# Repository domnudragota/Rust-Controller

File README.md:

# Project Name
GamePad/Controller
## Description

Simple GamePad built on a breadboard to test in games. Is built on Windows XInput API, so it will detect it as an XBOX Controller. The purpose of this project is (besides building a controller) to test input latency in different games and on different systems, computers and monitors in order to see the difference in input latency. Will also compare with an actual Xbox Series controller.

## Hardware

<!-- Fill out this table with all the hardware components that you mght need.

The format is 
```
| [Device](link://to/device) | This is used ... | [price](link://to/store) |

```

-->

| Device | Usage | Price |
|--------|--------|-------|
| [Rapspberry Pi Pico W](https://www.raspberrypi.com/documentation/microcontrollers/raspberry-pi-pico.html) | The microcontroller | [35 RON](https://www.optimusdigital.ro/en/raspberry-pi-boards/12394-raspberry-pi-pico-w.html) |
| BreadBoard | Build the circuit | [10 RON] https://www.optimusdigital.ro/ro/prototipare-breadboard-uri/8-breadboard-830-points.html |
| Buttons ( 12-15 ) | Input for controller | [5 RON] https://www.optimusdigital.ro/ro/butoane-i-comutatoare/1119-buton-6x6x6.html?search_query=buton&results=222 |
| Resistances | To not fry the circuit | [5 RON] https://www.optimusdigital.ro/ro/componente-electronice-rezistoare/858-rezistor-025w-18k.html?search_query=rezistor&results=120 |
| 2x JoySticks | Move and aim with the controller | [10 RON] https://www.optimusdigital.ro/ro/senzori-senzori-de-atingere/742-modul-joystick-ps2-biaxial-negru-cu-5-pini.html?search_query=joystick&results=42 |

## Links

<!-- Add a few links that got you the idea and that you think you will use for your project -->

1. [link](https://learn.microsoft.com/en-us/windows/win32/xinput/getting-started-with-xinput)
2. [link](https://www.howtogeek.com/792984/directinput-vs.-xinput-for-game-controllers-whats-the-difference/)
...

# Software and Code

### Rust Code for Raspberry Pi Pico W
The Rust code deployed on the Raspberry Pi Pico W reads button presses and joystick movements, packaging them into a structured format to be sent over UDP.

## Run the code
* Open the lab-main-Copy-Copy file in which IDE you desire (I used RustRover for this project)
* The code is located in /lab08/lab08_ex3_4/src/main.rs

⚠️ **Warning:** Ensure change the IP adresses and the path target to the cyw43-firmware in the code before you build it. Also the ID and the password of the network. Make sure the band of the network is 2.4GHZ!

```rust
let fw = include_bytes!("C:/Users/Andrei/Desktop/lab-main/cyw43-firmware/43439A0.bin");
let clm = include_bytes!("C:/Users/Andrei/Desktop/lab-main/cyw43-firmware/43439A0_clm.bin");

```

```rust
//change the ip adress as well

match socket
            .send_to(
                &packet,
                //here
                IpEndpoint::new(IpAddress::v4(192, 555, 553, 555), 1234), 
            )
            .await
        {
            Ok(()) => {
                info!("sent")
            }
            Err(e) => {
                warn!("send error: {:?}", e);
            }
        }
        info!("Sending packet to UDP server...");

        //match for joystick
        match socket.send_to(&packet, IpEndpoint::new
        //and here
        (IpAddress::v4(192, 555, 555, 555), 1234)).await {
            Ok(()) => info!("Joystick data sent"),
            Err(e) => warn!("send error: {:?}", e),
         }

    }
```
```rust
//change the network

const WIFI_NETWORK: &str = "da";
const WIFI_PASSWORD: &str = "da";
```

## Building the code
* Open a terminal and make sure you are in the correct directory 

⚠️ **Warning:** Please double check if the terminal correctly detects the directory (including the -Copy - Copy sufixes of the name), otherwise it won't build correctly

* To make sure you are in the correct file, use these commands

```
cd '.\lab-main - Copy - Copy\lab08\lab08_ex3_4\
```
* To build the project, simply type in the terminal
```
cargo build --release --target=thumbv6m-none-eabi  
```
* When it compiles, we need to open an UDP server so that we can send the data.
* Open the _udpserver_ file as a **separate** project/tab.
* Run the server with _cargo run_
* Once the server is fully loaded, go back to the 1st project and type in the terminal in order to flash it on the Pico

```
elf2uf2-rs -d -s ..\..\target\thumbv6m-none-eabi\release\lab08_ex3_4

```
* When the Pico connects to the UDP server, it will constantly send packets to the server
* Now we need a "translator" to decode the packets

# Detecting the Controller on Windows

## Prerequisites

Before you begin setting up the project, ensure you have the following prerequisites installed on your system:

## System Requirements
- **Operating System**: Windows 10 or newer is recommended for full compatibility.

## Software Requirements
- **.NET Framework**: .NET 5.0 or later. Make sure to download and install it from [Microsoft's official site](https://dotnet.microsoft.com/download).
- **Visual Studio** or **Visual Studio Code**: For code editing and debugging. Visual Studio can be downloaded from [here](https://visualstudio.microsoft.com/downloads/).

## Driver Installation
- **ViGEmBus Driver**: This driver is required to create a virtual Xbox controller that the system recognizes.
  - Download the latest version of the ViGEmBus driver from the [ViGEmBus GitHub releases page](https://github.com/ViGEm/ViGEmBus/releases).
  - Follow the installation instructions provided there to install the driver on your system.

## Additional Libraries
- **Nefarius.ViGEm.Client**: This is a .NET library used to interact with the ViGEmBus driver programmatically.
  - Ensure your project references this library. It can be added via NuGet in Visual Studio or by running the following command in your project directory:
    ```bash
    dotnet add package Nefarius.ViGEm.Client
    ```

## Hardware Requirements
- If testing the project physically, ensure you have a compatible hardware setup, including a game controller or custom hardware interfacing with your PC.

Make sure all prerequisites are properly installed and configured before proceeding with the project setup.

# Opening the Project and Adding NuGet Packages

## Opening the C# Project in Visual Studio

To start working on the project, you need to open it in an Integrated Development Environment (IDE). Visual Studio is recommended for C# projects. Follow these steps to open the project:

1. **Launch Visual Studio**:
   - Open Visual Studio. If you haven't installed it yet, download it from [Visual Studio Downloads](https://visualstudio.microsoft.com/downloads/).

2. **Open Project or Solution**:
- Name of the C# code is _ConsoleApp1_
   - On the initial launch screen, click **Open a project or solution**.
   - Navigate to the folder where you have cloned or downloaded the project.
   - Select the `.sln` or `.csproj` file and click **Open** to load the project into Visual Studio.

## Adding a NuGet Package

NuGet is a package manager for .NET that enables developers to share and consume useful code. Adding a NuGet package to your project can extend its functionality easily. Here's how to add a NuGet package:

1. **Open NuGet Package Manager**:
   - Right-click on the project in the **Solution Explorer** in Visual Studio.
   - Click **Manage NuGet Packages**.

2. **Browse for Packages**:
   - Go to the **Browse** tab in the NuGet Package Manager.
   - Type the package name you want to install in the search box (e.g., `Nefarius.ViGEm.Client`).

3. **Install the Package**:
   - Select the package from the list of search results.
   - Click on the **Install** button next to the package details.
   - Review any license agreements, if prompted, and accept them to proceed with the installation.

4. **Verify Package Installation**:
   - After installation, the package will appear under the **Dependencies** > **NuGet** node in your project structure.
   - You can now use the functionalities provided by the NuGet package in your project code.

## Verifying the Setup

After opening the project and adding the necessary NuGet packages, build the project to verify that everything is set up correctly:

- Click on **Build** > **Build Solution** in the menu bar.
- Ensure that the build completes without errors.

Before running the code, make sure to clode **ONLY** the UDP server in Rust, as C# will throw an exception.

# Mapping the buttons
* Run the C# code and it will display all the "translated" packages that the PICO is sending. 
## Step 1: Connect Your USB Controller

First, you need to physically connect your USB controller to your Windows machine.

- **Plug the USB connector** of your controller into a free USB port on your computer.
- Wait for Windows to recognize the device and install any necessary drivers. This process is typically automatic.

## Step 2: Check Device Recognition

After connecting your controller, verify that Windows has recognized it.

- Open **Control Panel** by typing `Control Panel` in the Start menu and pressing Enter.
- Navigate to **Hardware and Sound** > **Devices and Printers**.
- Under **Devices**, look for your USB controller. It should be listed under "Devices" if Windows recognizes it properly.
- If Device Manager can't find it, search in the Start menu for "Set Up USB Controllers".

## Step 3: Calibrate Your Controller

To ensure optimal performance, you might need to calibrate your controller. Here’s how to do it:

- Right-click on your controller icon in **Devices and Printers** and select **Game controller settings**.
- In the Game Controllers window, select your controller and click **Properties**.
- In the Properties window, go to the **Settings** tab and click on **Calibrate**.
- Follow the on-screen instructions to complete the calibration process.

## Step 4: Test Your Controller

After calibration, it’s a good idea to test the controller to make sure all buttons and joysticks are working as expected.

- In the Properties window of your controller, switch to the **Test** tab.
- Test each button and joystick on your controller. As you press buttons and move joysticks, corresponding buttons should light up in the test screen, confirming their functionality.

That's pretty much it. Let me know if there are questions regarding the compilation process.

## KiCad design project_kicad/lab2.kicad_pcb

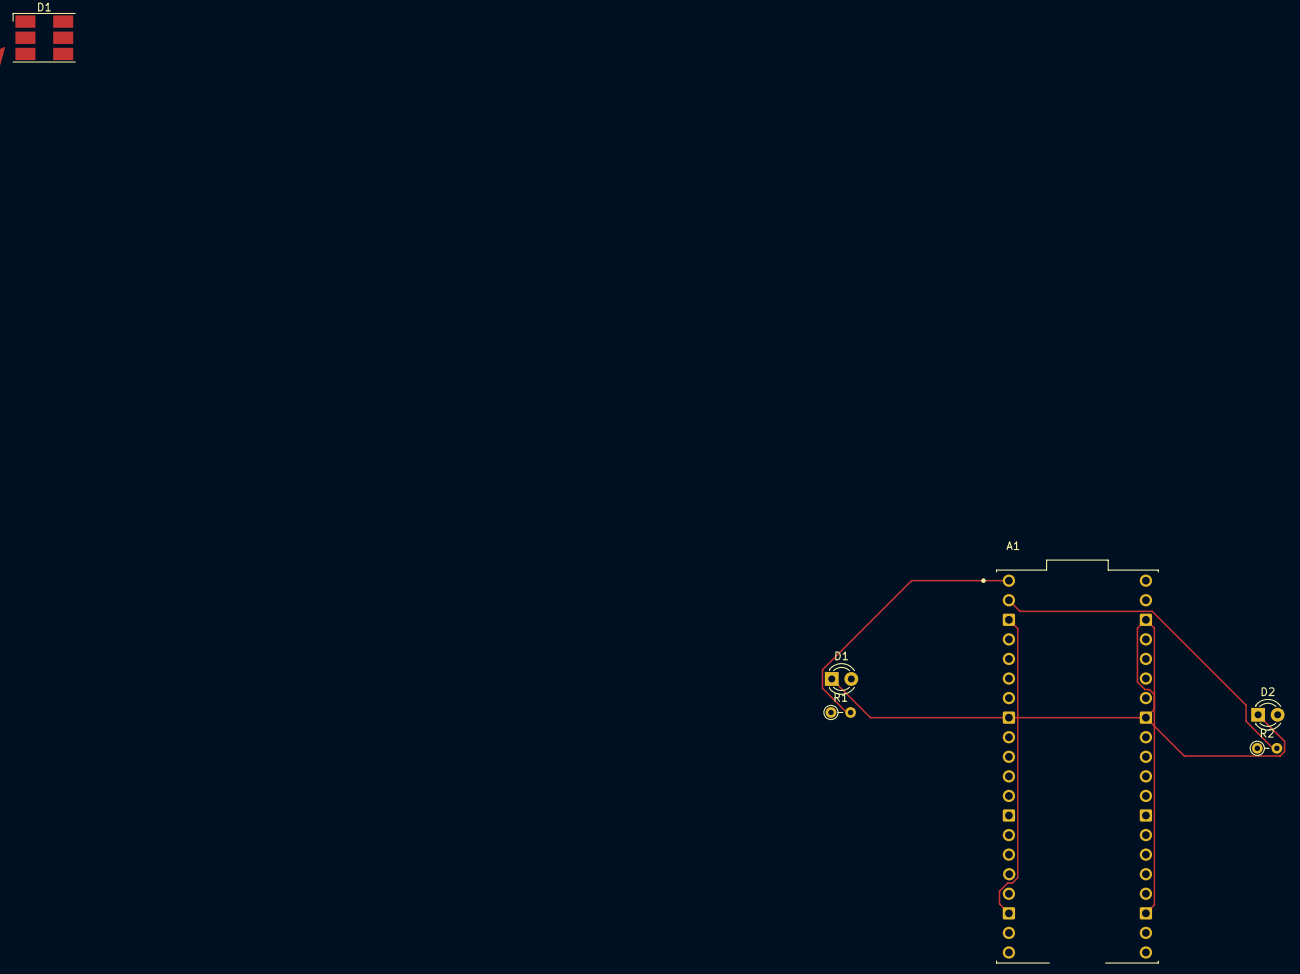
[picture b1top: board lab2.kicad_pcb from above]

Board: 2 copper layers, 7 parts (0 on the bottom side), 5 nets.

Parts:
A1: SC0918; MODULE_SC0918
D1, D2: LED; LED_D3.0mm
D1#2: LED_ARGB; LED_RGB_Cree-PLCC-6_6x5mm_P2.1mm
R1, R2: R; R_Axial_DIN0204_L3.6mm_D1.6mm_P2.54mm_Vertical
RN1: VoltageDivider; Symbol_HighVoltage_NoTriangle_6x15mm_Copper

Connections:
GND: A1.3 (GND), A1.8 (GND), A1.13 (GND), A1.18 (GND), A1.23 (GND), A1.28 (GND), A1.33 (AGND), A1.38 (GND), D1.1 (K), D2.1 (K)
unnamed: A1.2 (GP1), D1#2.1 (A)
unnamed: A1.4 (GP2), R2.2
unnamed: D1.2 (A), R1.1
unnamed: D2.2 (A), R2.1

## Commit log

2024-07-05 project description
2024-07-05 project files
2025-02-07 hardware implementation
